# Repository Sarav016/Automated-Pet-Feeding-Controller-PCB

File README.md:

# Automated-Pet-Feeding-Controller-PCB

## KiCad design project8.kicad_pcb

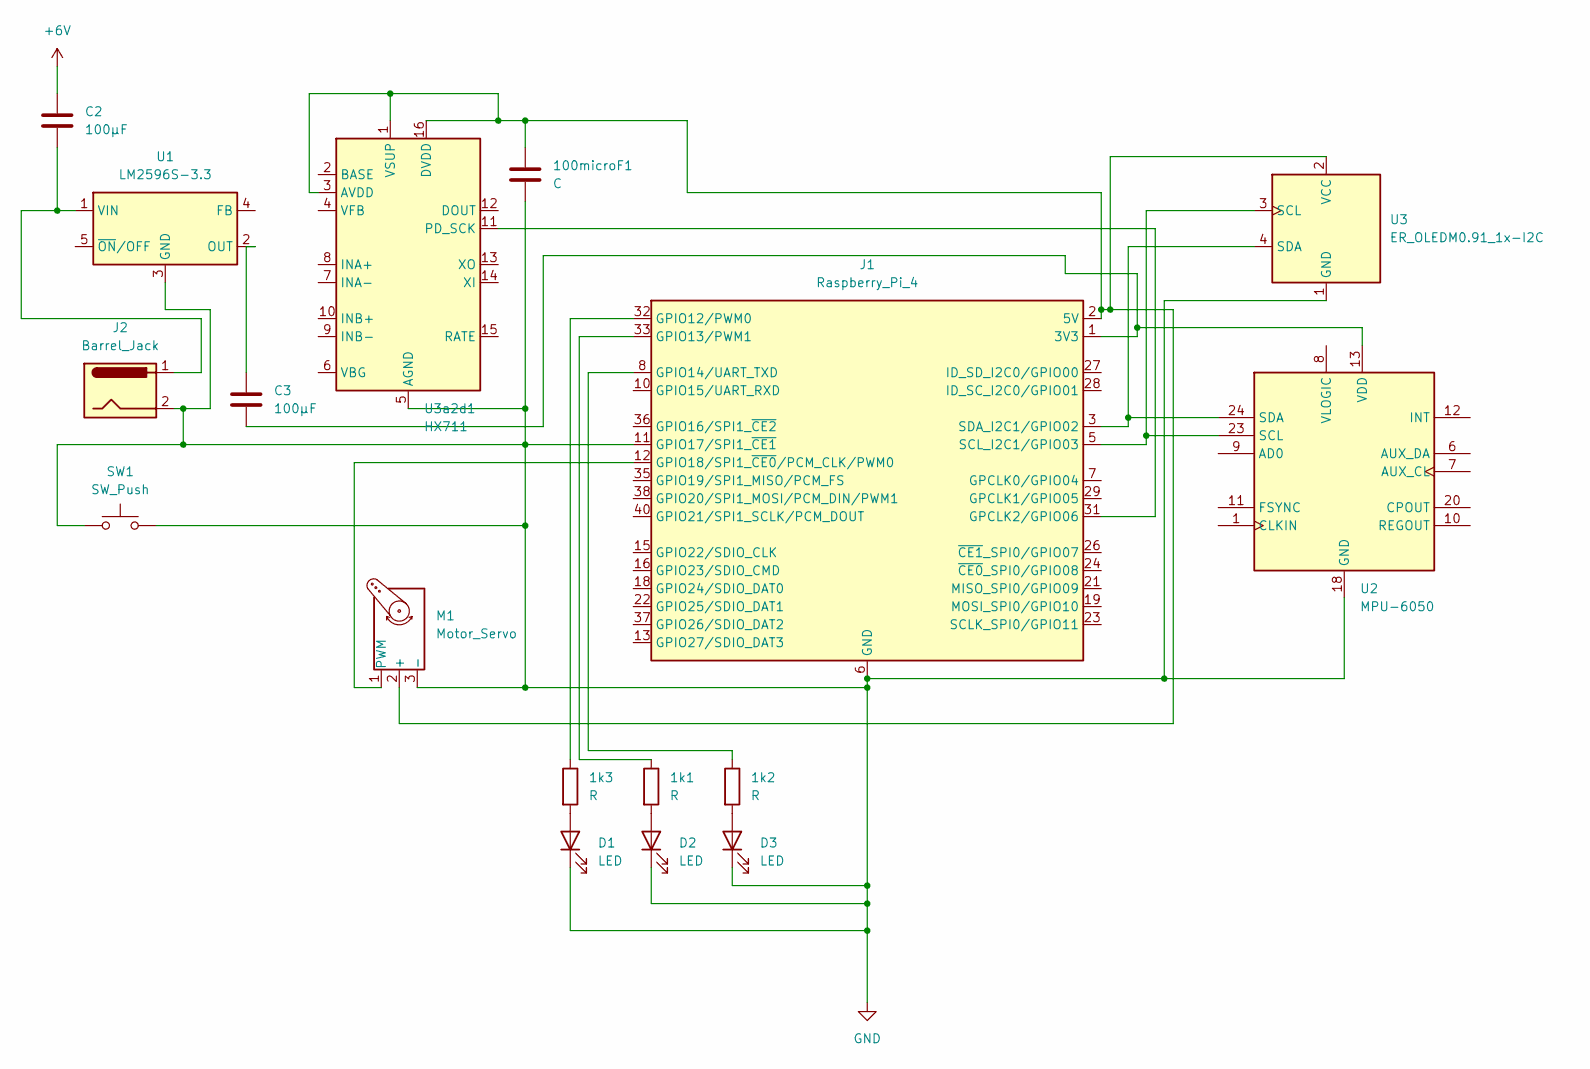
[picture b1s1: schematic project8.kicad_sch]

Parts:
1k1, 1k2, 1k3: R; R_Axial_DIN0204_L3.6mm_D1.6mm_P1.90mm_Vertical
100microF1: C; CP_Axial_L10.0mm_D4.5mm_P15.00mm_Horizontal
C2, C3: 100µF; CP_Axial_L10.0mm_D4.5mm_P15.00mm_Horizontal
D1, D2, D3: LED; LED_D5.0mm_Horizontal_O1.27mm_Z3.0mm
J1: Raspberry_Pi_4; Raspberry_Pi_Zero_Socketed_THT_FaceDown_MountingHoles
J2: Barrel_Jack; BarrelJack_CUI_PJ-036AH-SMT_Horizontal
M1: Motor_Servo; PinHeader_1x03_P2.54mm_Vertical
SW1: SW_Push; SW_PUSH_6mm
U1: LM2596S-3.3; TO-263-5_TabPin3
U2: MPU-6050; InvenSense_QFN-24_4x4mm_P0.5mm
U3: ER_OLEDM0.91_1x-I2C
U3a2d1: HX711; SOIC-16_3.9x9.9mm_P1.27mm

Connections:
+6V: C2.1
GND: 100microF1.2, D1.1 (K), D2.1 (K), D3.1 (K), J1.6 (GND), J1.9 (GND), J1.11 (GPIO17/SPI1_~CE1), J1.14 (GND), J1.20 (GND), J1.25 (GND), J1.30 (GND), J1.34 (GND), J1.39 (GND), J2.2, M1.3 (-), SW1.1, SW1.2, U1.3 (GND), U2.18 (GND), U3.1 (GND), U3a2d1.5 (AGND)
unnamed: 1k3.2, D1.2 (A)
unnamed: 1k1.2, D2.2 (A)
unnamed: 1k2.2, D3.2 (A)
unnamed: J1.31 (GPCLK2/GPIO06), U3a2d1.11 (PD_SCK)
unnamed: 1k3.1, J1.32 (GPIO12/PWM0)
unnamed: 1k1.1, J1.33 (GPIO13/PWM1)
unnamed: 1k2.1, J1.8 (GPIO14/UART_TXD)
unnamed: J1.12 (GPIO18/SPI1_~CE0/PCM_CLK/PWM0), M1.1 (PWM)
unnamed: J1.5 (SCL_I2C1/GPIO03), U2.23 (SCL), U3.3 (SCL)
unnamed: J1.3 (SDA_I2C1/GPIO02), U2.24 (SDA), U3.4 (SDA)
unnamed: 100microF1.1, J1.2 (5V), J1.4 (5V), M1.2 (+), U3.2 (VCC), U3a2d1.1 (VSUP), U3a2d1.3 (AVDD), U3a2d1.16 (DVDD)
unnamed: C3.1, U1.2 (OUT)
unnamed: C2.2, J2.1, U1.1 (VIN)
unnamed: C3.2, J1.1 (3V3), J1.17 (3V3), U2.13 (VDD)

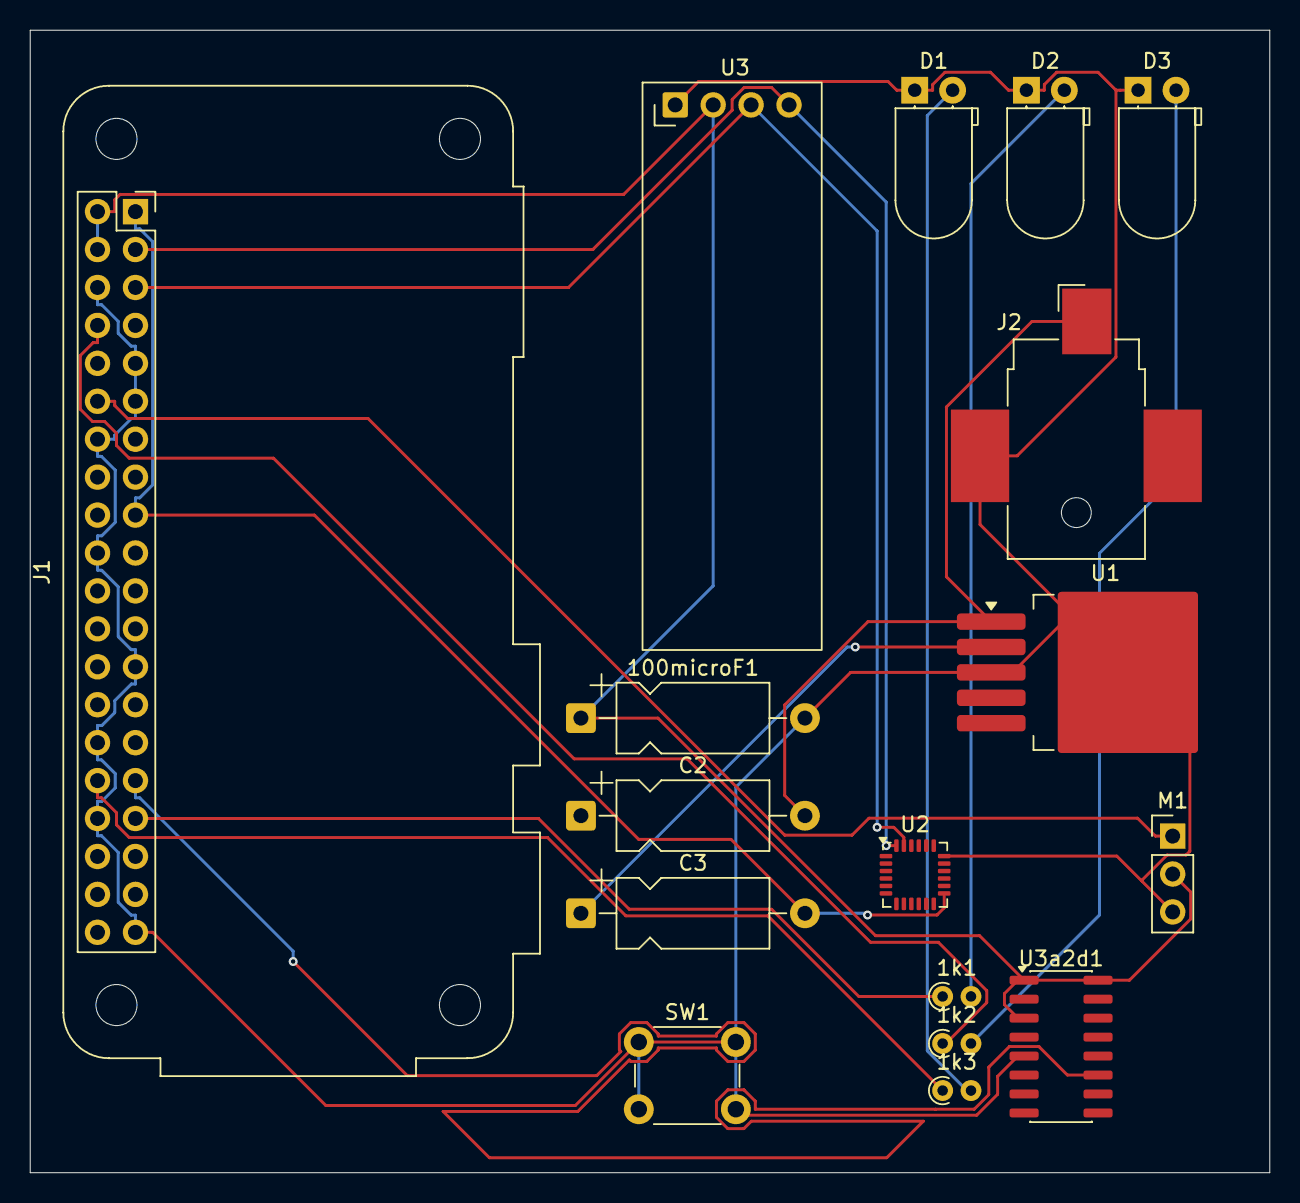
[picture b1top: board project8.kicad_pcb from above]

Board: 2 copper layers, 83.0 x 76.5 mm, 17 parts (0 on the bottom side), 15 nets.

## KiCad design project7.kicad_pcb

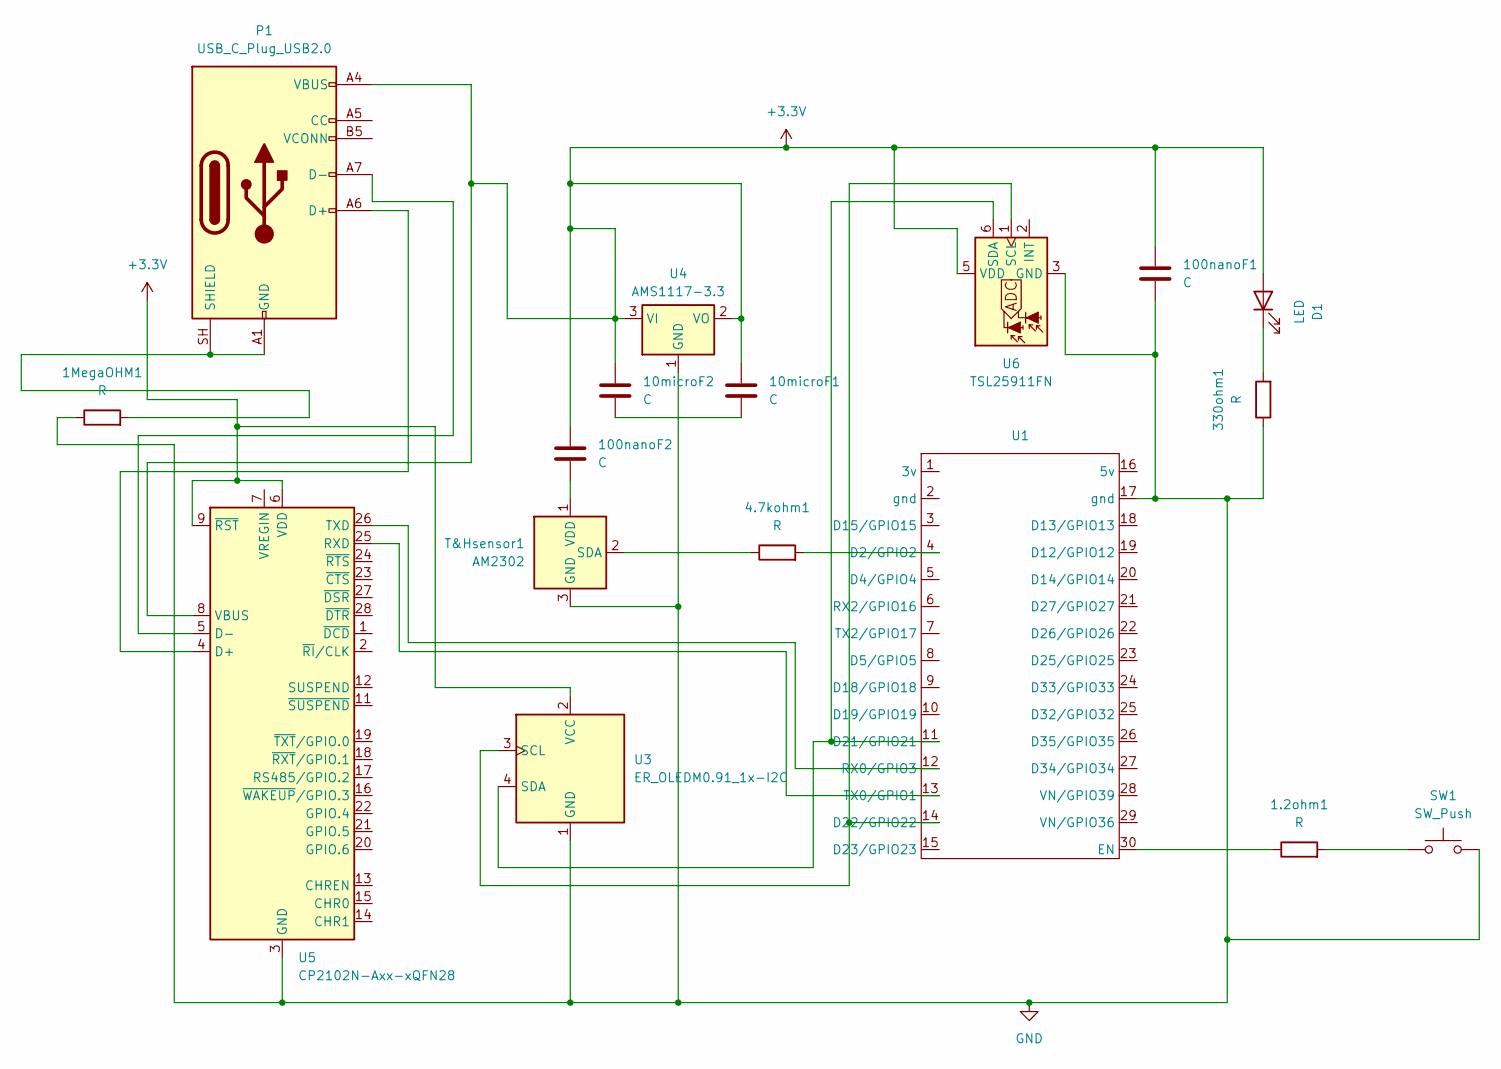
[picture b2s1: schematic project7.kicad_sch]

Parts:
1.2ohm1, 1MegaOHM1, 4.7kohm1, 330ohm1: R; R_Axial_DIN0204_L3.6mm_D1.6mm_P1.90mm_Vertical
10microF1, 10microF2, 100nanoF1, 100nanoF2: C; CP_Axial_L10.0mm_D4.5mm_P15.00mm_Horizontal
D1: LED; LED_D3.0mm_Horizontal_O1.27mm_Z6.0mm
P1: USB_C_Plug_USB2.0; USB_C_Receptacle_JAE_DX07S024WJ1R350
SW1: SW_Push; SW_PUSH_1P1T_6x3.5mm_H5.0_APEM_MJTP1250
T&Hsensor1: AM2302; ASAIR_AM2302_P2.54mm_Vertical
U1: esp32 devkit footprint
U3: ER_OLEDM0.91_1x-I2C
U4: AMS1117-3.3; SOT-223-3_TabPin2
U5: CP2102N-Axx-xQFN28; QFN-28-1EP_5x5mm_P0.5mm_EP3.35x3.35mm
U6: TSL25911FN; AMS_TSL25911FN

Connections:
+3.3V: 10microF1.1, 10microF2.2, 100nanoF1.2, 100nanoF2.2, D1.2 (A), P1.A4 (VBUS), P1.A9 (VBUS), P1.B4 (VBUS), P1.B9 (VBUS), U3.2 (VCC), U4.2 (VO), U4.3 (VI), U5.6 (VDD), U5.8 (VBUS), U5.9 (~RST), U6.5 (VDD)
GND: 1MegaOHM1.1, 100nanoF1.1, 330ohm1.1, SW1.2, T&Hsensor1.3 (GND), T&Hsensor1.4 (GND), U1.17 (gnd), U3.1 (GND), U4.1 (GND), U5.3 (GND), U5.29 (GND), U6.3 (GND)
unnamed: 1.2ohm1.2, SW1.1
unnamed: 10microF1.2, 10microF2.1
unnamed: 330ohm1.2, D1.1 (K)
unnamed: P1.A6 (D+), U5.4 (D+)
unnamed: P1.A7 (D-), U5.5 (D-)
unnamed: 1MegaOHM1.2, P1.A1 (GND), P1.A12 (GND), P1.B1 (GND), P1.B12 (GND), P1.SH (SHIELD)
unnamed: 4.7kohm1.1, T&Hsensor1.2 (SDA)
unnamed: 100nanoF2.1, T&Hsensor1.1 (VDD)
unnamed: 4.7kohm1.2, U1.4 (D2/GPIO2)
unnamed: U1.11 (D21/GPIO21), U3.4 (SDA), U6.6 (SDA)
unnamed: U1.14 (D22/GPIO22), U3.3 (SCL), U6.1 (SCL)
unnamed: 1.2ohm1.1, U1.30 (EN)
unnamed: U1.12 (RX0/GPIO3), U5.26 (TXD)
unnamed: U1.13 (TX0/GPIO1), U5.25 (RXD)

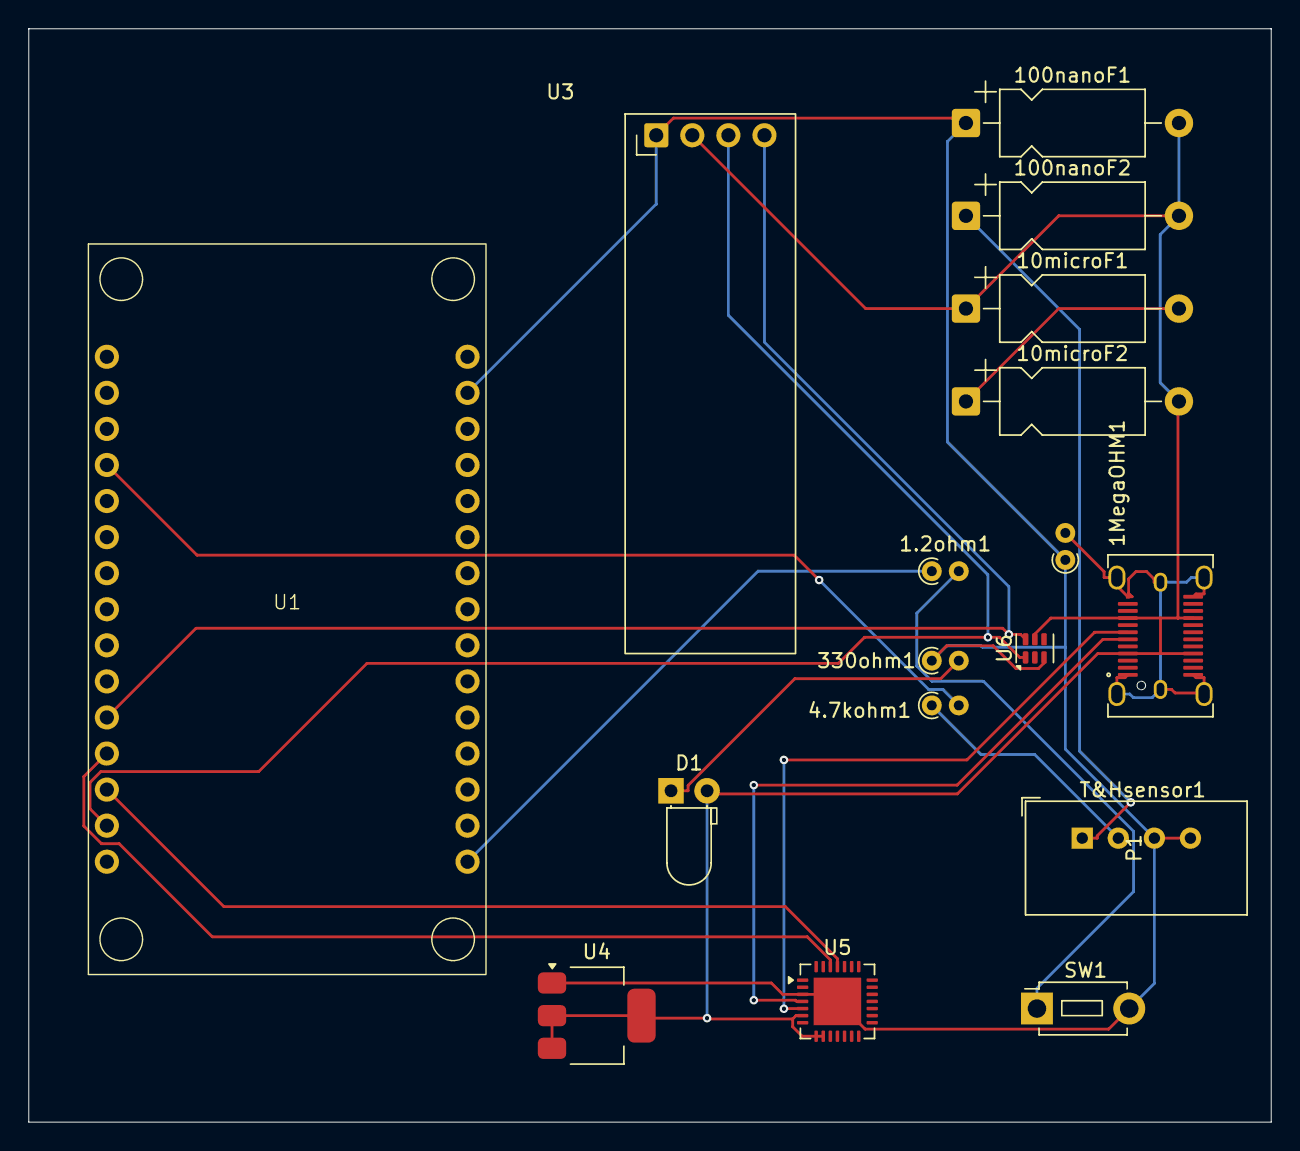
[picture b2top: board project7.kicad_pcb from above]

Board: 2 copper layers, 87.5 x 77.0 mm, 17 parts (0 on the bottom side), 16 nets.
